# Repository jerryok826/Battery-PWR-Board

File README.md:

# Battery PWR Board

## Project Description
As systems and devices to test get smaller, large power supplies with their fans are often not required. The "Battery PWR Board" is a small board that can supply 5.0 amd/or 3.3 Volts. In a typical case two 18650 batteries may all that's required. The board can also run from a 9 volt battery or a wall wart. The on board PWR_OK LED is on when the 5.0 volt rail is within valid limits. Guaranting the batteries are ok. Since it can run from batteries and there is no active switching devices on board it is very low noise. 

### Project Status
The project is basically complete.

## Design Files
This project was designed with Kicad 7.X

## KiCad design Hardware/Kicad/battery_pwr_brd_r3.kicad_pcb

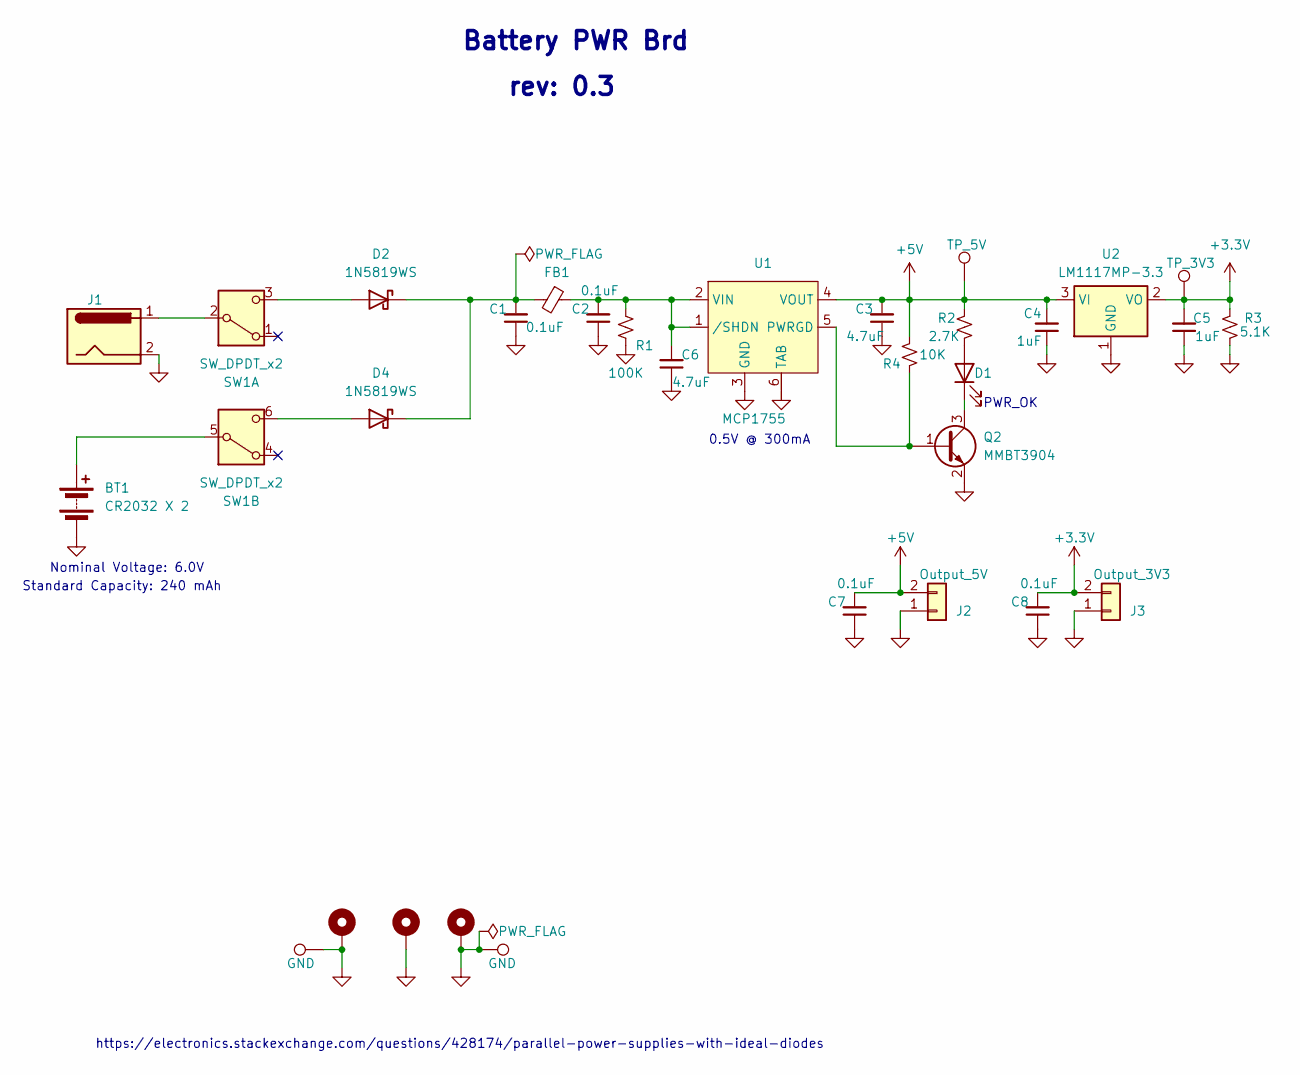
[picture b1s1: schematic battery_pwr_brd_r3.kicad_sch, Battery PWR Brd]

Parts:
BT1: CR2032 X 2; BatteryHolder_Keystone_103_1x20mm
C1, C2, C7, C8: 0.1uF; C_0805_2012Metric_Pad1.18x1.45mm_HandSolder
C3, C6: 4.7uF; C_0805_2012Metric_Pad1.18x1.45mm_HandSolder
C4, C5: 1uF; C_0805_2012Metric_Pad1.18x1.45mm_HandSolder
D1: OC_Fault; LED_1206_3216Metric_Pad1.42x1.75mm_HandSolder
D2, D4: 1N5819WS; D_SOD-123
FB1: FerriteBead, 6A 1 9mΩ 33Ω@100MHz ±25% 1206 Ferrit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; L_1206_3216Metric_Pad1.42x1.75mm_HandSolder
GND1, GND2: GND; TestPoint_THTPad_D2.0mm_Drill1.0mm
H1, H2, H3: MountingHole_Pad; MountingHole_3.2mm_M3_ISO7380_Pad_TopBottom
J1: INPUT_PWR; BarrelJack_GCT_DCJ200-10-A_Horizontal
J2: Output_5V
J3: Output_3V3
Q2: MMBT3904; SOT-23
R1: 100K; R_0805_2012Metric_Pad1.20x1.40mm_HandSolder
R2: 2.7K; R_0805_2012Metric_Pad1.20x1.40mm_HandSolder
R3: 5.1K; R_0805_2012Metric_Pad1.20x1.40mm_HandSolder
R4: 10K; R_0805_2012Metric_Pad1.20x1.40mm_HandSolder
SW1: SW_DPDT_x2; SW_DPDT_CK_JS202011JCQN
TP_3V1: TP_3V3; TestPoint_THTPad_D2.0mm_Drill1.0mm
TP_5V1: TP_5V; TestPoint_THTPad_D2.0mm_Drill1.0mm
U1: MCP1755; SOT-223-6
U2: LM1117MP-3.3; SOT-223-3_TabPin2

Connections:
+3.3V: C5.2, C8.2, J3.2, R3.2, TP_3V1.1, U2.2 (VO); also elsewhere on the board
+5V: C3.2, C4.2, C7.2, J2.2, R2.2, R4.2, TP_5V1.1, U1.4 (VOUT), U2.3 (VI); also elsewhere on the board
GND: BT1.2 (-), C1.1, C2.1, C3.1, C4.1, C5.1, C6.1, C7.1, C8.1, GND1.1, GND2.1, H1.1, H2.1, H3.1, J1.2, J2.1, J3.1, Q2.2 (E), R1.2, R3.1, U1.3 (GND), U1.6 (TAB), U2.1 (GND)
unnamed: BT1.1 (+), SW1.5 (B)
unnamed: D1.2 (A), R2.1
unnamed: D1.1 (K), Q2.3 (C)
unnamed: D2.2 (A), SW1.3 (C)
unnamed: C1.2, D2.1 (K), D4.1 (K), FB1.2
unnamed: D4.2 (A), SW1.6 (C)
unnamed: Q2.1 (B), R4.1, U1.5 (PWRGD)
unnamed: J1.1, SW1.2 (B)
unnamed: C2.2, C6.2, FB1.1, R1.1, U1.1 (/SHDN), U1.2 (VIN)

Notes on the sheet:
Standard Capacity: 240 mAh
rev: 0.3
0.5V @ 300mA
Battery PWR Brd
https://electronics.stackexchange.com/questions/428174/parallel-power-supplies-with-ideal-diodes
PWR_OK
Nominal Voltage: 6.0V

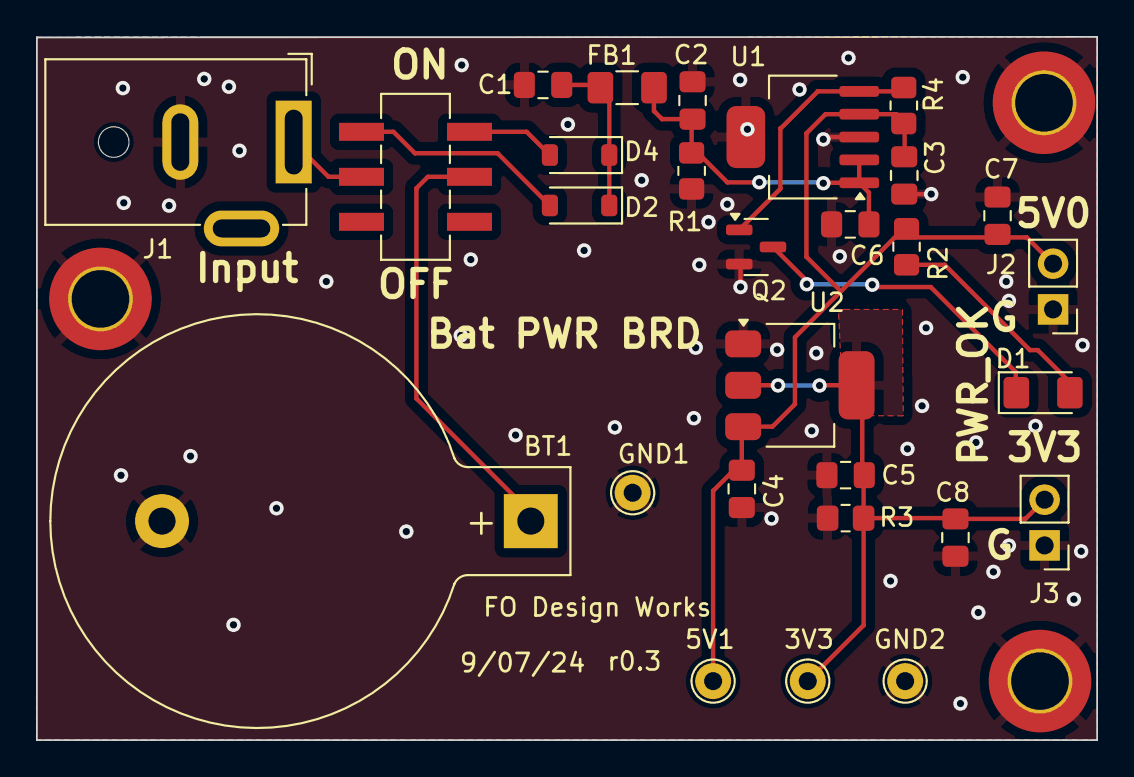
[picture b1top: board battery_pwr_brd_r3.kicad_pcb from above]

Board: 2 copper layers, 58.9 x 39.1 mm, 31 parts (0 on the bottom side), 12 nets.

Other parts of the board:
3V3: TP_3V3; TestPoint_THTPad_D2.0mm_Drill1.0mm
5V1: TP_5V; TestPoint_THTPad_D2.0mm_Drill1.0mm

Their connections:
+3.3V: 3V3.1; also elsewhere on the board
+5V: 5V1.1; also elsewhere on the board
